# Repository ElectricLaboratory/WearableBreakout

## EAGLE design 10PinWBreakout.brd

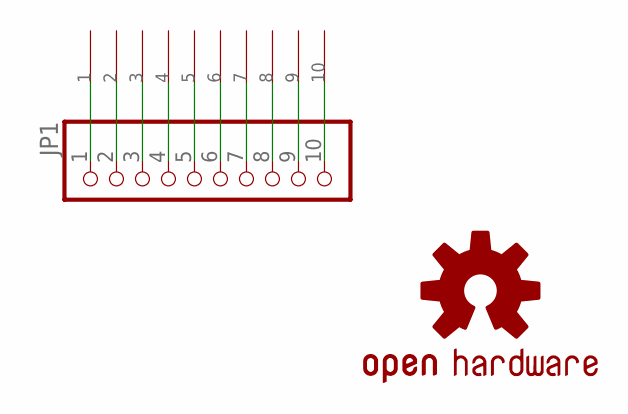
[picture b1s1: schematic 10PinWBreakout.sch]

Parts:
1, 2, 3, 4, 5, 6, 7, 8, 9, 10: SEWTAP-2.0IN; SEWINGTAP_2.0
JP1: PINHD-1X10; 1X10
U$2: OSHW-LOGOS; OSHW-LOGO-S

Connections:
unnamed: 1.P$1, JP1.1
unnamed: 2.P$1, JP1.2
unnamed: 3.P$1, JP1.3
unnamed: 4.P$1, JP1.4
unnamed: 5.P$1, JP1.5
unnamed: 6.P$1, JP1.6
unnamed: 7.P$1, JP1.7
unnamed: 8.P$1, JP1.8
unnamed: 9.P$1, JP1.9
unnamed: 10.P$1, JP1.10

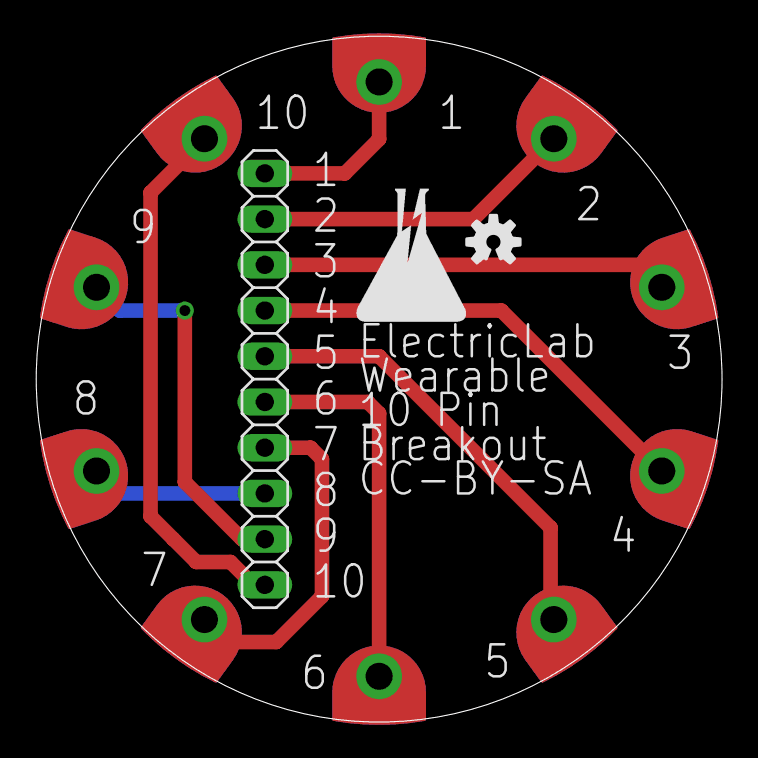
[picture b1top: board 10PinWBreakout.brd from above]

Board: 2 copper layers, 38.1 x 38.1 mm, 13 parts (0 on the bottom side), 10 nets.

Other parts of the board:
U$1: EL-LOGO

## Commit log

2013-06-15 Add PDFs

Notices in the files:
10PinWBreakout.brd:
CC-BY-SA
parts and their libraries:
SparkFun-Aesthetics: Licensing: CC v3.0 Share-Alike You are welcome to use this library for commercial purposes.
